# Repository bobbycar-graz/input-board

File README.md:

# input-board!
[kicad screenshot](input-board.png)

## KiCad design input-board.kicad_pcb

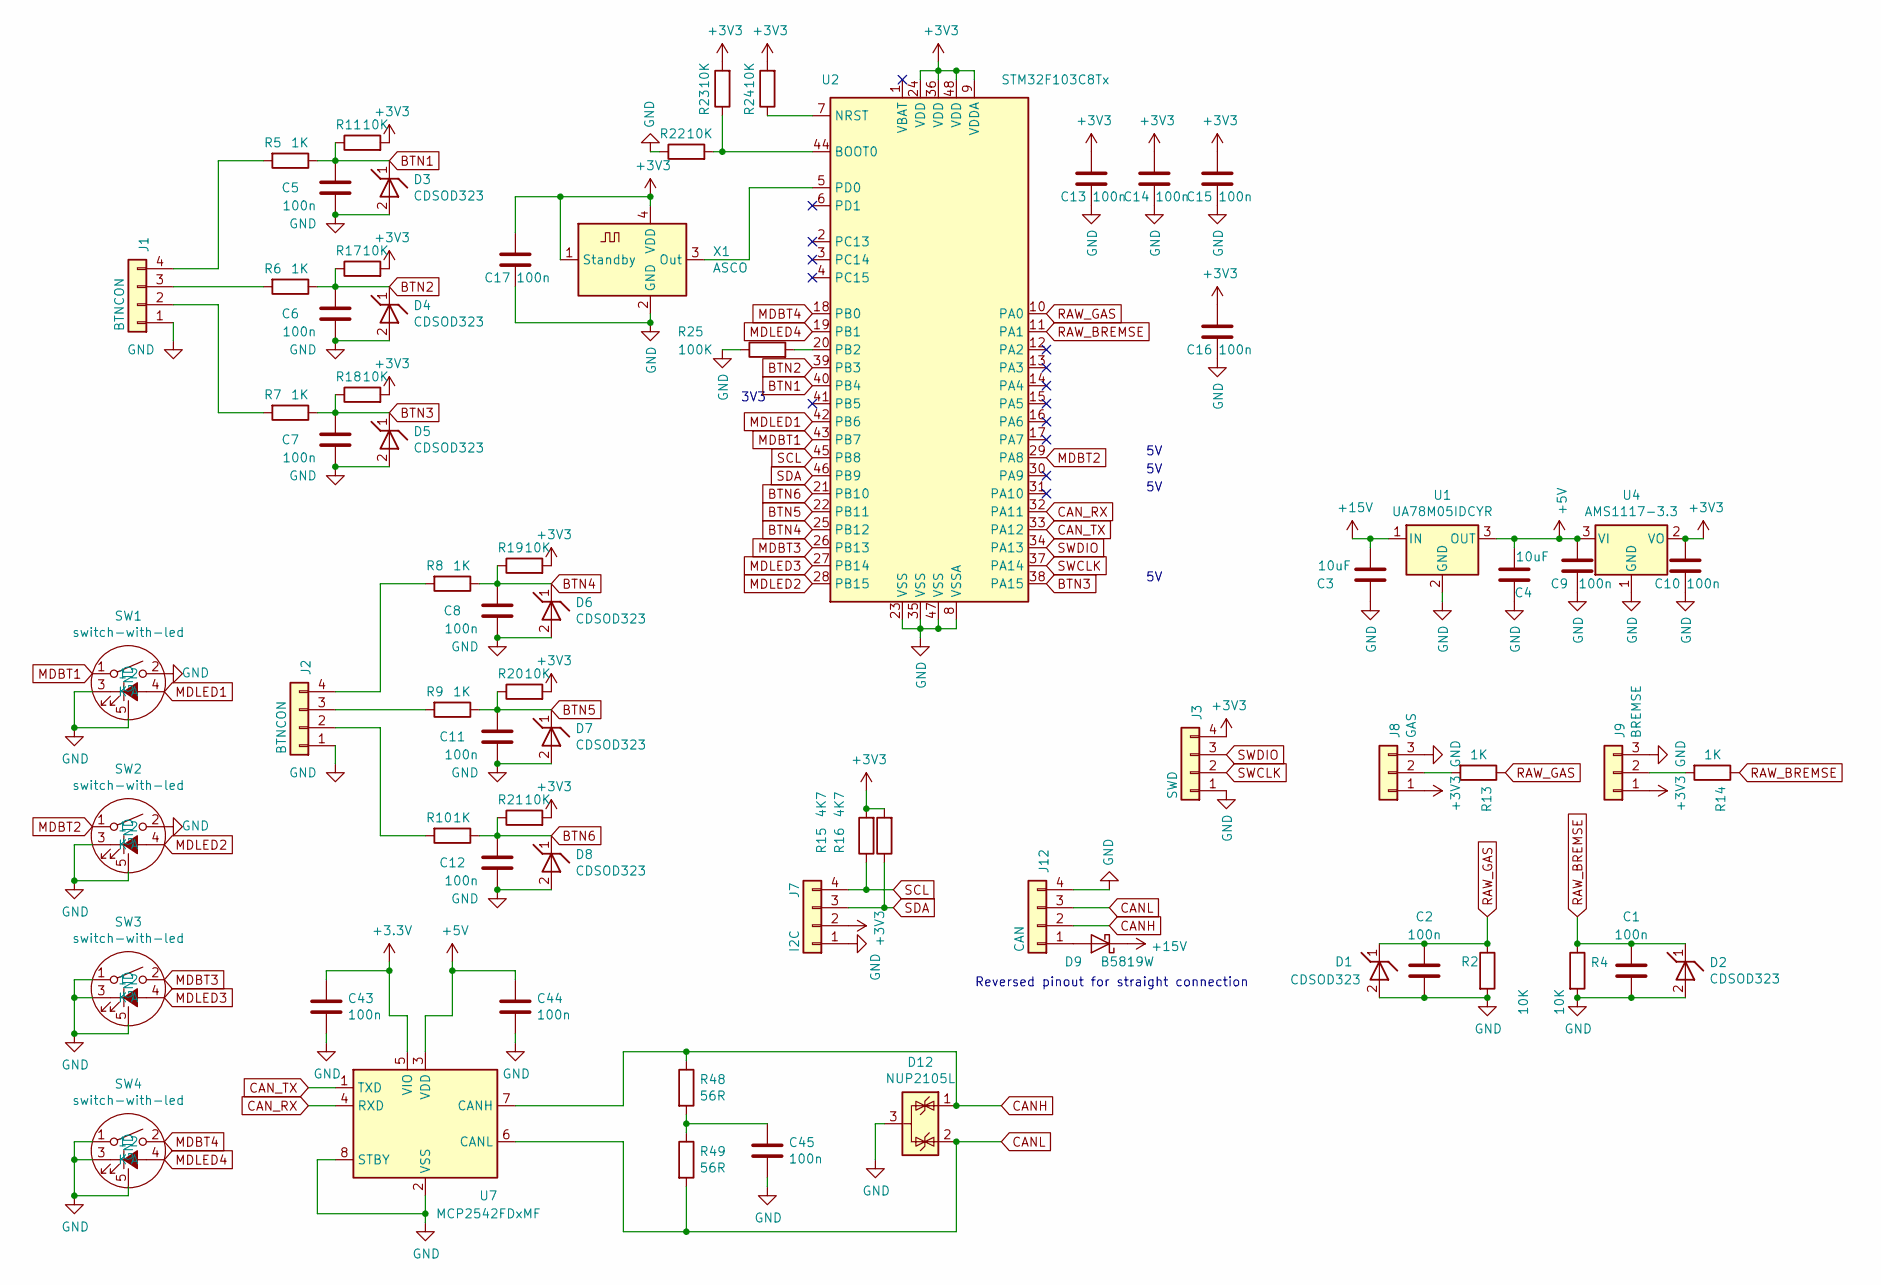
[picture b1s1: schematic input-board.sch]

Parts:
C1, C2, C5, C6, C7, C8, C9, C10, C11, C12, C13, C14, C15, C16, C17, C43, C44, C45: 100n; C_0603_1608Metric; LCSC Part # C14663
C3, C4: 10uF; C_0805_2012Metric; LCSC Part # C15850
D1, D2, D3, D4, D5, D6, D7, D8: CDSOD323; D_SOD-323; LCSC Part # C127526
D9: B5819W; D_SOD-123; LCSC Part # C8598
D12: NUP2105L; SOT-23; LCSC Part # C284104
J1, J2: BTNCON; Molex_PicoBlade_53048-0410_1x04_P1.25mm_Horizontal
J3: SWD; PinHeader_1x04_P2.54mm_Vertical
J7: I2C; JST_SH_SM04B-SRSS-TB_1x04-1MP_P1.00mm_Horizontal
J8: GAS; PinHeader_1x03_P2.54mm_Horizontal
J9: BREMSE; PinHeader_1x03_P2.54mm_Horizontal
J12: CAN; Molex_PicoBlade_53048-0410_1x04_P1.25mm_Horizontal
R2, R4, R11, R17, R18, R19, R20, R21, R22, R23, R24: 10K; R_0603_1608Metric; LCSC Part # C25804
R5, R6, R7, R8, R9, R10, R13, R14: 1K; R_0603_1608Metric; LCSC Part # C21190
R15, R16: 4K7; R_0603_1608Metric; LCSC Part # C23162
R25: 100K; R_0603_1608Metric; LCSC Part # C25803
R48, R49: 56R; R_0603_1608Metric; LCSC Part # C25196
SW1, SW2, SW3, SW4: switch-with-led; switch-16mm
U1: UA78M05IDCYR; SOT-223-3_TabPin2; LCSC Part # C182422
U2: STM32F103C8Tx; LQFP-48_7x7mm_P0.5mm; LCSC Part # C8304
U4: AMS1117-3.3; SOT-223-3_TabPin2; LCSC Part # C6186
U7: MCP2542FDxMF; DFN-8-1EP_3x3mm_P0.65mm_EP1.55x2.4mm
X1: ASCO; Oscillator_SMD_Abracon_ASDMB-4Pin_2.5x2.0mm; LCSC Part # C387448

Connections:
+5V: C4.2, C9.2, C44.1, U1.3 (OUT), U4.3 (VI), U7.3 (VDD)
+15V: C3.2, D9.1 (K), U1.1 (IN)
BTN1: C5.2, D3.1 (K), R5.1, R11.1, U2.40 (PB4)
BTN2: C6.2, D4.1 (K), R6.1, R17.1, U2.39 (PB3)
BTN3: C7.2, D5.1 (K), R7.1, R18.1, U2.38 (PA15)
BTN4: C8.2, D6.1 (K), R8.1, R19.1, U2.25 (PB12)
BTN5: C11.2, D7.1 (K), R9.1, R20.1, U2.22 (PB11)
BTN6: C12.2, D8.1 (K), R10.1, R21.1, U2.21 (PB10)
CANH: D12.1 (K), J12.2, R48.1, U7.7 (CANH)
CANL: D12.2 (K), J12.3, R49.2, U7.6 (CANL)
CAN_RX: U2.32 (PA11), U7.4 (RXD)
CAN_TX: U2.33 (PA12), U7.1 (TXD)
GND: C1.1, C2.1, C3.1, C4.1, C5.1, C6.1, C7.1, C8.1, C9.1, C10.1, C11.1, C12.1, C13.1, C14.1, C15.1, C16.1, C17.1, C43.2, C44.2, C45.2, D1.2 (A), D2.2 (A), D3.2 (A), D4.2 (A), D5.2 (A), D6.2 (A), D7.2 (A), D8.2 (A), D12.3 (A), J1.1, J2.1, J3.1, J7.1, J8.3, J9.3, J12.4, R2.2, R4.2, R22.1, R25.1, SW1.2, SW1.3 (K), SW1.5 (GND), SW2.2, SW2.3 (K), SW2.5 (GND), SW3.1, SW3.3 (K), SW3.5 (GND), SW4.1, SW4.3 (K), SW4.5 (GND), U1.2 (GND), U2.8 (VSSA), U2.23 (VSS), U2.35 (VSS), U2.47 (VSS), U4.1 (GND), U7.2 (VSS), U7.8 (STBY), U7.9 (VSS), X1.2 (GND)
MDBT1: SW1.1, U2.43 (PB7)
MDBT2: SW2.1, U2.29 (PA8)
MDBT3: SW3.2, U2.26 (PB13)
MDBT4: SW4.2, U2.18 (PB0)
MDLED1: SW1.4 (A), U2.42 (PB6)
MDLED2: SW2.4 (A), U2.28 (PB15)
MDLED3: SW3.4 (A), U2.27 (PB14)
MDLED4: SW4.4 (A), U2.19 (PB1)
unnamed: C45.1, R48.2, R49.1
unnamed: D9.2 (A), J12.1
unnamed: J1.2, R7.2
unnamed: J1.3, R6.2
unnamed: J1.4, R5.2
unnamed: J2.2, R10.2
unnamed: J2.3, R9.2
unnamed: J2.4, R8.2
unnamed: J8.2, R13.2
unnamed: J9.2, R14.2
unnamed: R22.2, R23.1, U2.44 (BOOT0)
unnamed: R24.1, U2.7 (NRST)
unnamed: R25.2, U2.20 (PB2)
unnamed: U2.5 (PD0), X1.3 (Out)
RAW_BREMSE: C1.2, D2.1 (K), R4.1, R14.1, U2.11 (PA1)
RAW_GAS: C2.2, D1.1 (K), R2.1, R13.1, U2.10 (PA0)
SCL: J7.4, R15.1, U2.45 (PB8)
SDA: J7.3, R16.1, U2.46 (PB9)
SWCLK: J3.2, U2.37 (PA14)
SWDIO: J3.3, U2.34 (PA13)

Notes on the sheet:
Reversed pinout for straight connection
3V3

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
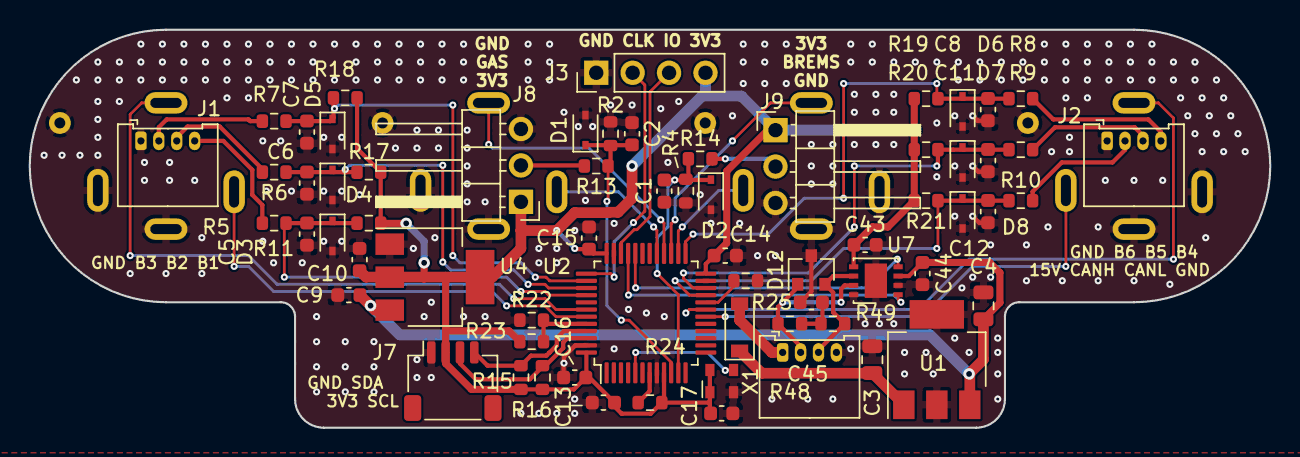
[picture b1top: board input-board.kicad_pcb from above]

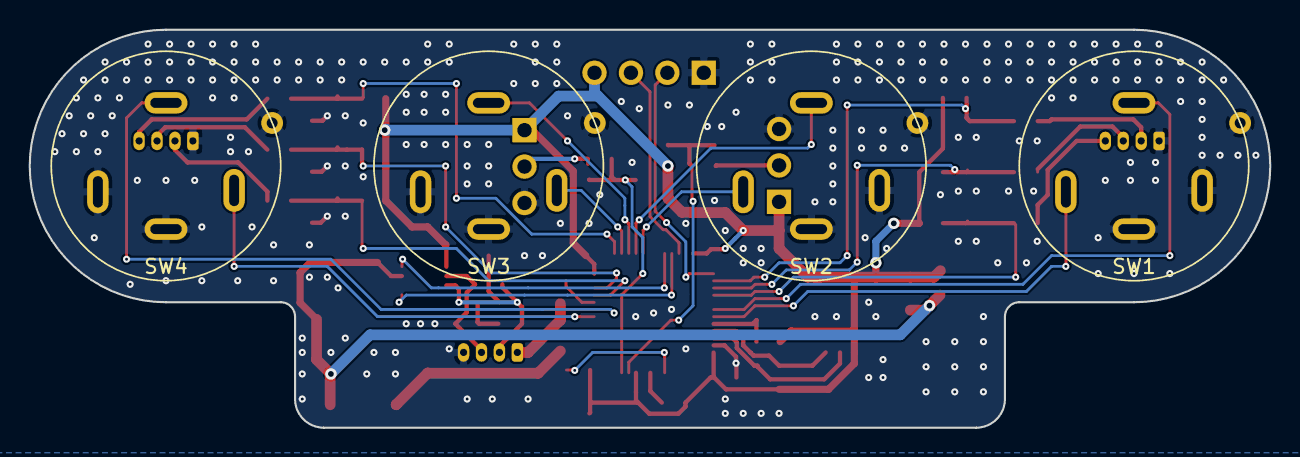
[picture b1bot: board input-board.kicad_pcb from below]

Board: 2 copper layers, 86.5 x 27.8 mm, 70 parts (4 on the bottom side), 42 nets.

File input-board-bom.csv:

Comment,Designator,Footprint,LCSC
"10uF","C3,C4","Capacitor_SMD:C_0805_2012Metric","C15850"
"100n","C1,C2,C5,C6,C7,C8,C9,C10,C11,C12,C13,C14,C15,C16,C17,C43,C44,C45","Capacitor_SMD:C_0603_1608Metric","C14663"
"CDSOD323","D1,D2,D3,D4,D5,D6,D7,D8","Diode_SMD:D_SOD-323","C127526"
"NUP2105L","D12","Package_TO_SOT_SMD:SOT-23","C284104"
"B5819W","D9","Diode_SMD:D_SOD-123","C8598"
"1K","R5,R6,R7,R8,R9,R10,R13,R14","Resistor_SMD:R_0603_1608Metric","C21190"
"4K7","R15,R16","Resistor_SMD:R_0603_1608Metric","C23162"
"100K","R25","Resistor_SMD:R_0603_1608Metric","C25803"
"10K","R2,R4,R11,R17,R18,R19,R20,R21,R22,R23,R24","Resistor_SMD:R_0603_1608Metric","C25804"
"56R","R48,R49","Resistor_SMD:R_0603_1608Metric","C25196"
"UA78M05IDCYR","U1","Package_TO_SOT_SMD:SOT-223-3_TabPin2","C182422"
"STM32F103C8Tx","U2","Package_QFP:LQFP-48_7x7mm_P0.5mm","C8304"
"AMS1117-3.3","U4","Package_TO_SOT_SMD:SOT-223-3_TabPin2","C6186"
"MCP2542FDxMF","U7","Package_DFN_QFN:DFN-8-1EP_3x3mm_P0.65mm_EP1.55x2.4mm",""
"ASCO","X1","Oscillator:Oscillator_SMD_Abracon_ASDMB-4Pin_2.5x2.0mm","C387448"

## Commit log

2021-02-16 initial commit no layout
2021-02-16 start of layout
2021-02-17 organizing parts on layout
2021-02-19 more component placing
2021-02-20 more layouting
2021-02-20 layout
2021-02-20 Layout prelim done
2021-02-20 added screenshot
2021-02-20 Added input reverse protection
2021-02-21 Changed input to LDO Added JLCPCB #
2021-02-21 Added nc to unused pins
2021-02-21 Exported manufacturing files Removed backup files
2021-02-22 made files production ready
2021-06-03 added schematic pdf
